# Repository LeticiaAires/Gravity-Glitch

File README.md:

# Gravity Glitch

## Introduction

Welcome to Gravity Glitch, an innovative project created by 7th-semester engineering students from École Nationale Supérieure de l'Électronique et de ses Applications (ENSEA). This project serves as a platform for hands-on learning in practical electronics, software development, project management, and teamwork.

## Project Objective

Our primary goal is to develop an exciting game inspired by the popular Flappy Bird game, with a unique twist – an innovative controller. We've integrated an infrared sensor into the game, which measures the distance between the player's hand and the sensor. This inventive controller allows players to guide "Flappy" through the game, helping it navigate obstacles and accumulate points.

## Getting Started

To get started with the project, follow these steps:

1. Clone the repository to your local machine:

   ```bash
   git clone https://github.com/LeticiaAires/Gravity-Glitch.git
   ```

2. Ensure you have the required dependencies installed.

   [VSCode](https://code.visualstudio.com/download)
 
   [Python]( https://www.python.org/downloads/)
 
   [PIP](https://bootstrap.pypa.io/get-pip.py)

3. How to play ?
   
   - Run the "main.py" file 
   
   - Click on the "Play" button to choose your pseudo and choose your game mode !

4. To launch the game without installing all modules and packages on your machine, create a virtual environment.

   - Create the environment 'my_env' inside the project directory :
     
      ```bash
      python -m venv my_environment
      ```

   - Activate the environment :
     
      ```bash
      my_environment/bin/activate
      ```

   - Install the required dependencies :
   
      ```bash
      pip install -r requirements.txt
      ```

   - Run the Game.py file and play !

   - Deactivate the environment :
     
      ```bash
      deactivate
      ```

## Features

- Flappy Bird-inspired gameplay with a unique controller.
- Innovative use of an infrared sensor for hand tracking.
- Challenging obstacles and addictive gameplay.
- Project designed and implemented by talented engineering students.

## Documentation
Here is an explanation of the game's structure : 

The "main.py" file is the file to run to start the Game. Then, we come across a window called "MainMenu" displaying the menu of the game (with the settings, play, quit, credits and rules buttons). From there, we can : 
- go to the settings/rules/credits windows who are self explanatory
- quit the game
- go to the play window
  
If you choose to do the later, then you will come across a first window asking for your name (to associate your score with your pseudo). From there you can either go back to the menu or continue and go choose your game mode (History mode or alternative = a more complex version of the flappy bird).
After that, by clicking on continue and pressing the space bar, you can start playing !
You have a "pause" button in the bottom left corner where you can go to the settings, see the best scores, restart, resume or quit the game. 
  
For more detailed information about the project, you can refer to the code itself. We have included comprehensive comments and documentation within the codebase to help you understand how everything works.

## License

This project is licensed under the [MIT License](LICENSE.md).

## Acknowledgments

We would like to express our gratitude to our instructors, mentors, and everyone who supported us throughout this project. Your guidance and encouragement were invaluable in making this project a reality.

## Collaborators

<table>
  <tr>
    <td align="center">
      <a href="#">
        
        <sub>
          <b>Anthony </b>
          </p>AnthonyDelille01     
        </sub>
      </a>
    </td>
    <td align="center">
      <a href="#">
        <br>
        <sub>
          <b>Cassandre   </b>
          </p>CassandreChandelier   
        </sub>
      </a>
      <td align="center">
      <a href="#">
        <br>
        <sub>
          <b>Douay Nicolas</b>
          </p>DBXYD
        </sub>
      </a>
    </td>
    <td align="center">
      <a href="#">
        <br>
        <sub>
          <b>Letícia Aires</b>
          </p>LeticiaAires
        </sub>
      </a>
    </td>
    <td align="center">
      <a href="#">
        <br>
        <sub>
          <b>Mael Doublet</b>
          </p>MaelDoublet
        </sub>
      </a>
      <td align="center">
      <a href="#">
        <br>
        <sub>
          <b>Mantou</b>
          </p>Mansko09
        </sub>
      </a>
<td align="center">
      <a href="#">
        <br>
        <sub>
          <b>Mathieu Daubercies</b>
          </p>MathieuDaubercies
        </sub>
      </a>
      <td align="center">
      <a href="#">
        <br>
        <sub>
          <b>Solène</b>
          </p>salom0701
        </sub>
      </a>
      <td align="center">
      <a href="#">
        <br>
        <sub>
          <b>Romain</b>
          </p>Romain04G
        </sub>
      </a>
      <td align="center">
      <a href="#">
        <br>
        <sub>
          <b>Zineb</b>
          </p>Ninevv
        </sub>
      </a>

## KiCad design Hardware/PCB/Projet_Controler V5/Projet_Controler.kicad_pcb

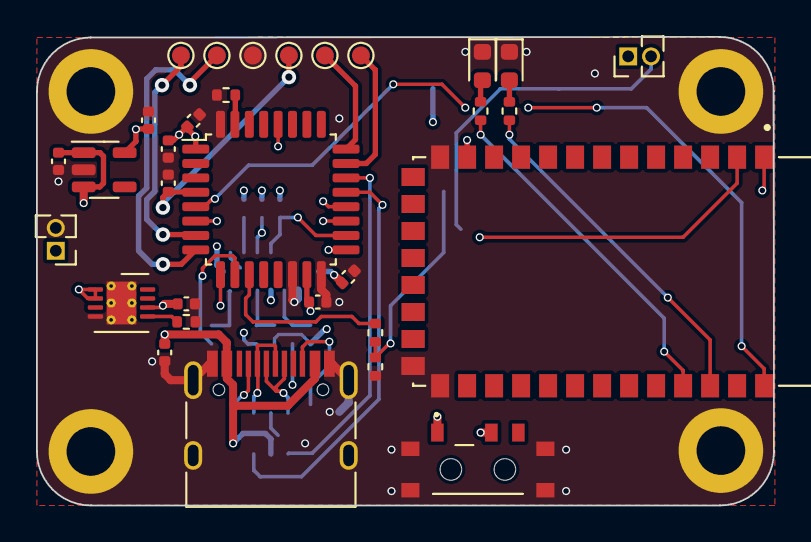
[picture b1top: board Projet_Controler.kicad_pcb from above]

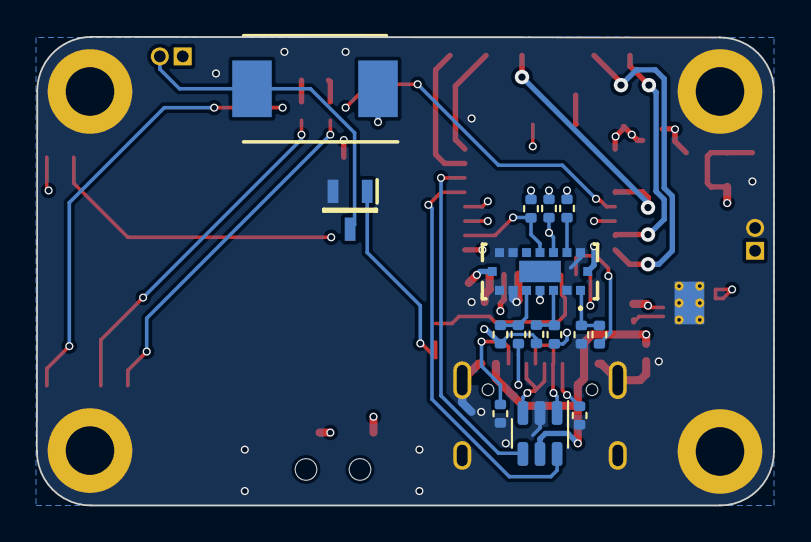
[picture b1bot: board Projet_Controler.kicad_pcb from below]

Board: 4 copper layers, 41.0 x 26.0 mm, 50 parts (15 on the bottom side), 37 nets.

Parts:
C201, C203, C204, C205: 100n; C_0402_1005Metric
C202: 4.7u; C_0402_1005Metric
C301, C302, C303: 1u; C_0402_1005Metric
C304: 220n; C_0402_1005Metric
D501, D502: LED; LED_0603_1608Metric
D601: VS-30BQ015HM3_9AT; DIOM7959X262N
GND201: TestPoint; TestPoint_Pad_D1.0mm
H101, H102, H103, H104: MountingHole_Pad; MountingHole_2.7mm_M2.5_DIN965_Pad
IC301: LTC4058EDD-4.2#PBF; DFN-8-1EP_3x3mm_P0.5mm_EP1.65x2.38mm_ThermalVias
IC**: VL53L5CX
J301: BATT; PinHeader_1x02_P1.27mm_Vertical
J302: USB_C_Receptacle_USB2.0; USB_C_Receptacle_HRO_TYPE-C-31-M-12
J601: MOTOR; PinHeader_1x02_P1.27mm_Vertical
NRST201: TestPoint; TestPoint_Pad_D1.0mm
Q601: SQ2310ES-T1; SOT95P237X112-3N
R201: 100k; R_0402_1005Metric
R301: 1.65k; R_0402_1005Metric
R302, R303: 5.1k; R_0402_1005Metric
R401, R402, R405: 1k; R_0402_1005Metric
R403, R404, R406, R407: 47k; R_0402_1005Metric
R408, R409, R602: 10k; R_0402_1005Metric
R501, R502: 820; R_0402_1005Metric
R601: 22; R_0402_1005Metric
S**: 450404015514
SWCLK201: TestPoint; TestPoint_Pad_D1.0mm
SWDIO201: TestPoint; TestPoint_Pad_D1.0mm
U201: STM32G431KBTx; LQFP-32_7x7mm_P0.8mm
U301: BU33SD5WG-TR; SOT-23-5
U302: WE-TVS-82400102; SOT-23-6
U501: HC-05; XCVR_HC-05
USART2_RX201, USART2_TX201: TestPoint; TestPoint_Pad_D1.0mm

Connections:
+3.3V: C202.1, C203.1, C204.1, C205.1, C302.1, D601.1 (K), IC**.A4, IC**.B1, IC**.B7, J601.1, R403.1, R404.1, R407.2, R408.1, R409.1, U201.1 (VDD), U201.15 (VDDA), U201.17 (VDD), U301.5 (OUT), U501.12 (3.3_VCC)
+5V: C303.1, C304.1, IC301.6 (VCC), J302.A4 (VBUS), J302.A9 (VBUS), J302.B4 (VBUS), J302.B9 (VBUS), U302.5
+BATT: C301.1, S**.1, U301.1 (IN), U301.3 (STBY)
/BLUETOOTH/KEY: U201.5 (PA0), U501.34 (PIO[11])
/BLUETOOTH/LED_1: R501.1, U501.31 (PIO[8])
/BLUETOOTH/LED_2: R502.1, U501.32 (PIO[9])
/BLUETOOTH/USART1_RX: U201.19 (PA9), U501.2 (UART-RX)
/BLUETOOTH/USART1_TX: U201.20 (PA10), U501.1 (UART-TX)
/MOTOR/MOTOR: D601.2 (A), J601.2, Q601.3 (D)
/MOTOR/PWM: R601.1, U201.11 (PA6)
/POWER/BAT: IC301.1 (BSENSE), IC301.2 (BAT), J301.1, S**.2
/POWER/USB_DM: U201.21 (PA11), U302.6
/POWER/USB_DP: U201.22 (PA12), U302.4
/SENSORS/I2C3_SCL: IC**.C4, R408.2, U201.18 (PA8)
/SENSORS/I2C3_SDA: IC**.C3, R409.2, U201.28 (PB5)
/SENSORS/TOF_I2C_RST: R405.2, U201.10 (PA5)
/SENSORS/TOF_INT: R401.2, U201.6 (PA1)
/SENSORS/TOF_LPn: R402.2, U201.9 (PA4)
/STM32/BOOT0: R201.1, U201.31 (PB8)
/STM32/NRST: C201.2, NRST201.1, U201.4 (PG10)
/STM32/SWCLK: SWCLK201.1, U201.24 (PA14)
/STM32/SWDIO: SWDIO201.1, U201.23 (PA13)
/STM32/USART2_RX: U201.7 (PA2), USART2_RX201.1
/STM32/USART2_TX: U201.8 (PA3), USART2_TX201.1
GND: C201.1, C202.2, C203.2, C204.2, C205.2, C301.2, C302.2, C303.2, C304.2, D501.1 (K), D502.1 (K), GND201.1, H101.1, H102.1, H103.1, H104.1, IC301.4 (GND), IC301.9 (EP), IC**.A2, IC**.A6, IC**.A7, IC**.C1, IC**.C6, IC**.C7, J301.2, J302.A1 (GND), J302.A12 (GND), J302.B1 (GND), J302.B12 (GND), J302.S1 (SHIELD), Q601.2 (S), R201.2, R301.2, R302.2, R303.1, R406.2, R602.2, S**.MP1, S**.MP2, S**.MP3, S**.MP4, U201.14 (VSSA), U201.16 (VSS), U201.32 (VSS), U301.2 (GND), U302.2, U501.13 (GND), U501.21 (GND), U501.22 (GND)
unnamed: D501.2 (A), R501.2
unnamed: D502.2 (A), R502.2
unnamed: IC301.5 (PROG), R301.1
unnamed: IC**.A1, R405.1, R406.1
unnamed: IC**.A3, R401.1, R403.2
unnamed: IC**.A5, R402.1, R404.2
unnamed: IC**.C2, R407.1
unnamed: J302.A5 (CC1), R302.1
unnamed: J302.B5 (CC2), R303.2
unnamed: J302.A6 (D+), J302.B6 (D+), U302.3
unnamed: J302.A7 (D-), J302.B7 (D-), U302.1
unnamed: Q601.1 (G), R601.2, R602.1

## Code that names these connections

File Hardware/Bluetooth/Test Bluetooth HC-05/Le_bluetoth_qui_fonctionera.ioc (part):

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Mcu.Name=STM32L476R(C-E-G)Tx
Mcu.Package=LQFP64
Mcu.UserName=STM32L476RGTx
PA10.Mode=Asynchronous
PA10.Signal=USART1_RX
PA13\ (JTMS-SWDIO).GPIOParameters=GPIO_Label
PA13\ (JTMS-SWDIO).GPIO_Label=TMS
PA13\ (JTMS-SWDIO).Mode=Serial_Wire
PA13\ (JTMS-SWDIO).Signal=SYS_JTMS-SWDIO
PA14\ (JTCK-SWCLK).GPIOParameters=GPIO_Label
PA14\ (JTCK-SWCLK).GPIO_Label=TCK
PA14\ (JTCK-SWCLK).Mode=Serial_Wire
PA14\ (JTCK-SWCLK).Signal=SYS_JTCK-SWCLK
PA2.GPIOParameters=GPIO_Speed,GPIO_PuPd,GPIO_Label,GPIO_Mode
PA2.GPIO_Label=USART_TX
PA2.GPIO_Mode=GPIO_MODE_AF_PP
PA2.GPIO_PuPd=GPIO_NOPULL
PA2.GPIO_Speed=GPIO_SPEED_FREQ_VERY_HIGH
PA2.Signal=USART2_TX
PA3.GPIOParameters=GPIO_Speed,GPIO_PuPd,GPIO_Label,GPIO_Mode
PA3.GPIO_Label=USART_RX
PA3.GPIO_Mode=GPIO_MODE_AF_PP
PA3.GPIO_PuPd=GPIO_NOPULL
PA3.GPIO_Speed=GPIO_SPEED_FREQ_VERY_HIGH
PA3.Signal=USART2_RX
PA5.GPIOParameters=GPIO_Speed,GPIO_PuPd,GPIO_Label,GPIO_ModeDefaultOutputPP
PA5.GPIO_Label=LD2 [green Led]
PA5.GPIO_ModeDefaultOutputPP=GPIO_MODE_OUTPUT_PP
PA5.GPIO_PuPd=GPIO_NOPULL
PA5.GPIO_Speed=GPIO_SPEED_FREQ_LOW
PA5.Signal=GPIO_Output
PA9.Mode=Asynchronous
PA9.Signal=USART1_TX
PB3\ (JTDO-TRACESWO).GPIOParameters=GPIO_Label
PB3\ (JTDO-TRACESWO).GPIO_Label=SWO
PB3\ (JTDO-TRACESWO).Signal=SYS_JTDO-SWO
PC13.GPIOParameters=GPIO_PuPd,GPIO_Label,GPIO_ModeDefaultEXTI
PC13.GPIO_Label=B1 [Blue PushButton]
PC13.GPIO_ModeDefaultEXTI=GPIO_MODE_IT_FALLING
PC13.GPIO_PuPd=GPIO_NOPULL
PC13.Signal=GPXTI13
PC14-OSC32_IN\ (PC14).Mode=LSE-External-Oscillator
PC14-OSC32_IN\ (PC14).Signal=RCC_OSC32_IN
PC15-OSC32_OUT\ (PC15).Mode=LSE-External-Oscillator
PC15-OSC32_OUT\ (PC15).Signal=RCC_OSC32_OUT
PH0-OSC_IN\ (PH0).Signal=RCC_OSC_IN
PH1-OSC_OUT\ (PH1).Signal=RCC_OSC_OUT
RCC.HSE_VALUE=8000000
RCC.SYSCLKFreq_VALUE=80000000
RCC.SYSCLKSource=RCC_SYSCLKSOURCE_PLLCLK
board=NUCLEO-L476RG
boardIOC=true

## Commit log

2023-10-03 Create Assets
2023-10-05 Create Test
2023-10-10 resources
    Nucleo board and TOF resources
2023-10-10 Add resources
    Interesting links to program I2C
2023-10-10 I2C sources
2023-10-16 Add files via upload
    First shot of the game'smenu
2023-10-17 Update .~lock.Links.odt#
2023-10-17 new background
2023-10-17 adding import sys
2023-10-17 updated the menu (added the quit button)
2023-10-17 zinebs firts commit
2023-10-17 API sources
2023-10-17 added the options display
2023-10-17 API Functions
2023-10-18 I added music + made some changes in the menu
2023-10-18 music files
2023-10-18 Tried to fix the music when musicoff is pressed
2023-10-19 created the game file + modified the menu
2023-10-20 Uploading previously deleted file
    please don't delete it anymore:)
2023-10-22 Updated name file History.Game.py to credits.py
2023-10-23 started creating the game + changed pic formats
2023-10-23 deleted game tests
2023-10-24 placed bg, bird etc in assets
2023-10-24 changed paths
2023-10-24 test
2023-10-24 creating mkdocs
2023-10-24 rules
2023-10-24 fixed the music problem
2023-10-24 deleted tp music
2023-10-24 game_for_mantou
2023-10-28 Added the play window
2023-11-05 created classes in the newmenu
2023-11-07 Create vl53l0x doc
2023-11-07 rules menu
2023-11-07 added the credits from solene
2023-11-07 depose code Cassandre et asset utilisés
2023-11-07 added the rules
2023-11-11 added the possibility to enter user's name
2023-11-11 linked the game to the History mode
2023-11-11 change one title and deleted unecessary comments
2023-11-14 ajout du code du jour
2023-11-14 sensor_ranging
2023-11-14 subjects
2023-11-24 created file for each class
2023-11-25 Create custom
2023-11-25 Renamed some files, and corrected things
2023-11-25 Trying to fix the circular issue
2023-11-26 fixed bugs
2023-11-26 tof ranging
2023-11-27 small changes to make pause window work
2023-11-27 initialized only once in main file pygame
2023-11-27 trying to fix the pausewindow issue
2023-11-28 tof updates
2023-11-28 deleted unecessary things
2023-11-28 deleted copy
2023-11-28 added game name to README.md
2023-11-28 renamed cassandre README.md
2023-11-28 added some comments
2023-11-28 cache
2023-11-28 Created text files
2023-11-28 Created Rules text
2023-11-28 added variable game_state
2023-11-28 fixing bugs
2023-12-05 Create Datasheet
2023-12-05 deleted the game_state variable
2023-12-05 Organisation
2023-12-05 Datasheet
2023-12-05 Anglais
2023-12-05 safely deleted the pycache doublons
2023-12-05 fixing quit button in pause menu
2023-12-05 Diapo + Structure
2023-12-05 Bluetooth
    Creation du dossier Bluetooth et ajout de documentation
2023-12-05 can now display the pseudo after entering it
2023-12-05 added the custom window to the play menu
2023-12-05 added comment to point at problem
2023-12-12 added the custom menu to the play menu
2023-12-12 Rules text file and access test, requirements file for virtual environment
2023-12-19 fixed quit button
2023-12-19 added the scores window
2023-12-19 game exit fix
2023-12-19 bug fixing
2023-12-19 bug fix
2023-12-19 Reorganisation
2023-12-19 fiz sys.exit and fix costumes
2024-01-16 game.py correction and pipe + collision inserted
2024-01-16 Update README.md
    Virtual environment tutorial
2024-01-16 venv tuto correction :)
2024-01-19 enormous structural change and debugging
2024-01-21 menu reestructure
2024-01-21 menu reestructuration
2024-01-21 game.py optimization
2024-01-23 inhence menu efficiency
2024-01-23 bug correction
2024-01-23 increase efficiency
2024-01-23 code fix
2024-01-23 game fix
2024-02-27 bird speed fix
2024-02-27 add bluetooth stm32 project
2024-02-27 add stm32 project for HC-05
2024-03-05 Ajout du projet STM32 du test blutooth HC-05
2024-03-05 kit2
2024-03-05 Ajout DOC commandes AT
2024-03-05 update pcb
2024-03-18 fixing rules
2024-03-18 credits fix
2024-03-18 menu fix
2024-03-18 custom menu start fix
2024-03-18 make bird easier
2024-03-19 custom fix
2024-03-19 PCB V4
2024-03-19 reroutage LF pas assumé à 100%
2024-03-26 PCB V5
2024-03-26 add gnd via
2024-03-26 Supports 3D
